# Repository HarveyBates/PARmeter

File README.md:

# PARmeter
## Introduction

**P**hotosynthetic **A**ctive **R**adiation (**PAR**) meters are designed to measure light intensity that has a wavelength between ~400 and 700 nm. This range represents the usable range for photosynthesising organims. This information is important for (amongst other things):

1. Studying photosynthesis
2. Calibrating plant growth light fixtures
3. Calibrating aqurarium LED arrays 

Readings are usually represented as the number of moles of photons per meter squared per second (**&mu;E m<sup>-2</sup> s<sup>-1</sup>** or **&mu;mol m<sup>-2</sup> s<sup>-1</sup>**). 

PAR meters differ from **l**uminous fl**ux** (**lux**) meters in that lux meters are typically used to measure wavelengths specific to human vision rather than those avaliable to photosynthesising organisms. Unlike PAR meters, lux meters require different coefficents for different light sources (white light, warm white light, blue, green, cyan etc.); therefore, they need to be calibrated for each light quality used. 

### Photodiode response

PAR meters are quite expensive when compared to lux meters as PAR meters require a virtually flat spectral response between the 400 and 700 nm wavelength range. This spectral response depends upon the photodiode used for detection. Typically, photodiodes have a varied wavelength specific response and as such only a few have ideal characteristics for PAR meters.

For this design I am using the [FDS100](https://www.thorlabs.com/thorproduct.cfm?partnumber=FDS100) (Silicon Photodiode) from ThorLabs. As its response is farily linear through the wavelength ranges of PAR. The increase in responsitivity with increasing wavelength is as a result of increasing [photon energy](https://en.wikipedia.org/wiki/Photon_energy).

### Cutoff filter

As can be seen from the photodiode responsitivity figure, the FDS100 photodiode is very responsive in wavelengths greater than 700 nm, therefore it is important that a short-pass filter is used to block these wavelengths from reaching the detector. 

Here I am using a 750 nm [short-pass filter](https://www.edmundoptics.com/p/750nm-125mm-dia-od-20-shortpass-filter/43482/) from Edmund optics. 750 nm is greater than the 400 - 700 nm range I mentioned earlier. However, the PAR range that is commonly used was determined a long time ago and there is evidence in the literature that IR-wavlengths are important to photosynthesis.

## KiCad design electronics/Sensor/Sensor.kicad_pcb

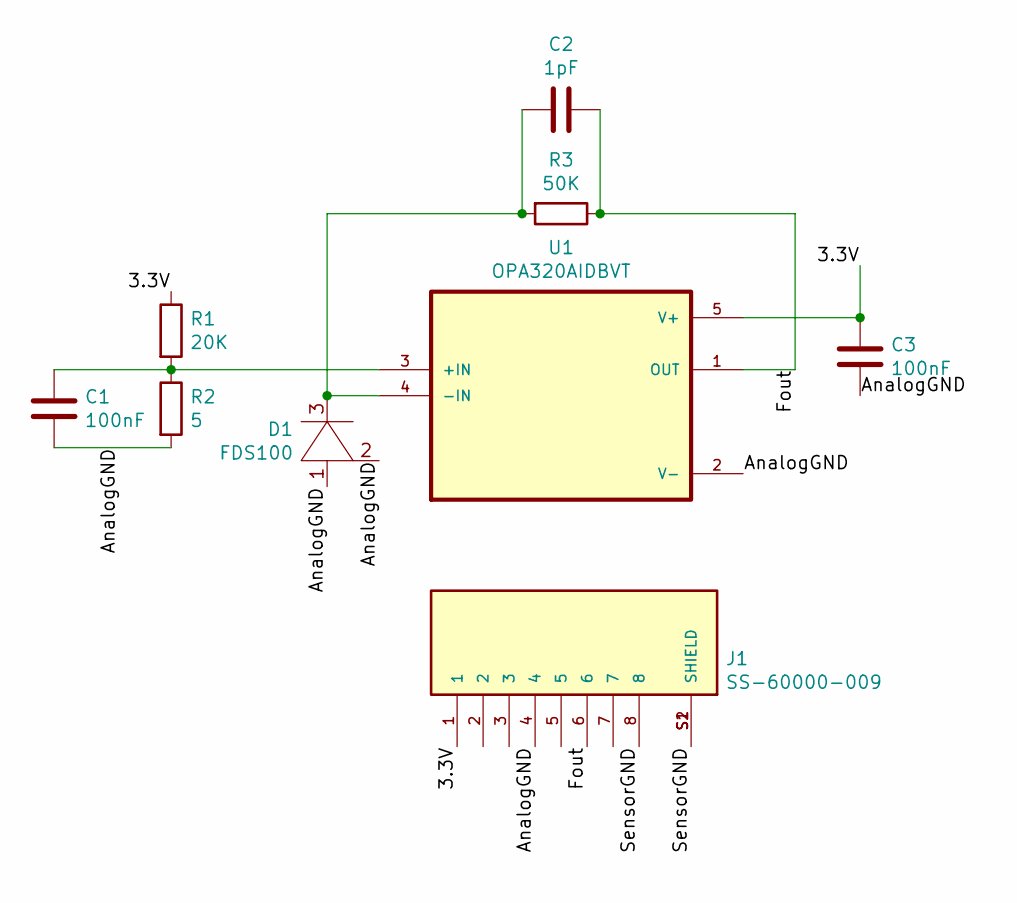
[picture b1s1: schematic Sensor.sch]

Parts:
C1, C3: 100nF; C_0805_2012Metric_Pad1.18x1.45mm_HandSolder
C2: 1pF; C_0805_2012Metric_Pad1.18x1.45mm_HandSolder
D1: FDS100
J1: SS-60000-009; BEL_SS-60000-009; PARTREV D4
R1: 20K; R_0805_2012Metric_Pad1.20x1.40mm_HandSolder
R2: 5; R_0805_2012Metric_Pad1.20x1.40mm_HandSolder
R3: 50K; R_0805_2012Metric_Pad1.20x1.40mm_HandSolder
U1: OPA320AIDBVT; OPA320AIDBVT5-SOT-23

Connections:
/3.3V: C3.2, J1.1, R1.1, U1.5 (V+)
/AnalogGND: C1.2, C3.1, D1.1, D1.2, J1.4, R2.2, U1.2 (V-)
/Fout: C2.1, J1.6, R3.1, U1.1 (OUT)
/SensorGND: J1.8, J1.S1 (SHIELD), J1.S2 (SHIELD)
unnamed: C1.1, R1.2, R2.1, U1.3 (+IN)
unnamed: C2.2, D1.3, R3.2, U1.4 (-IN)

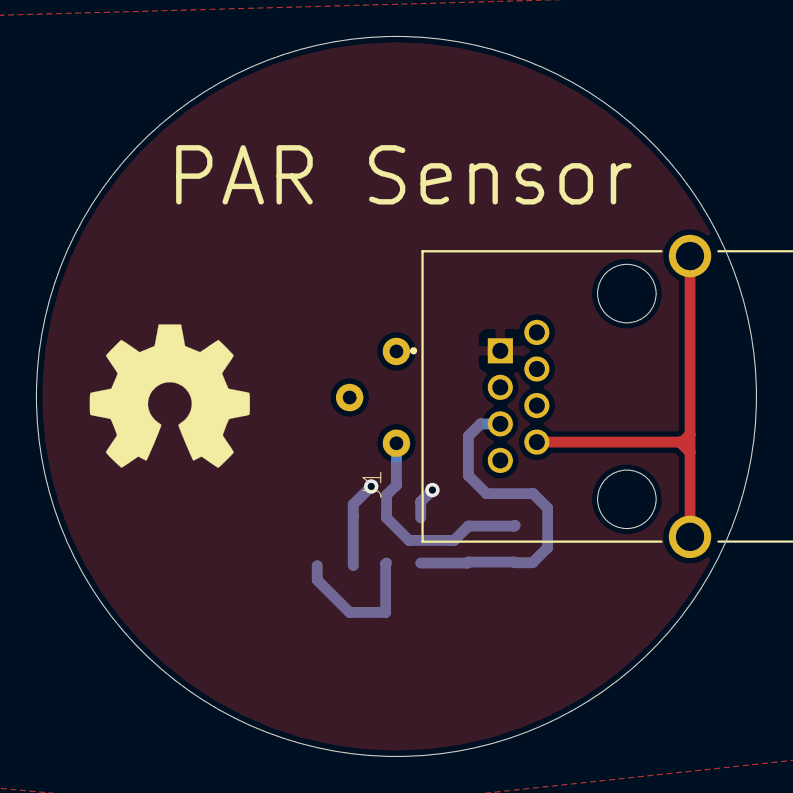
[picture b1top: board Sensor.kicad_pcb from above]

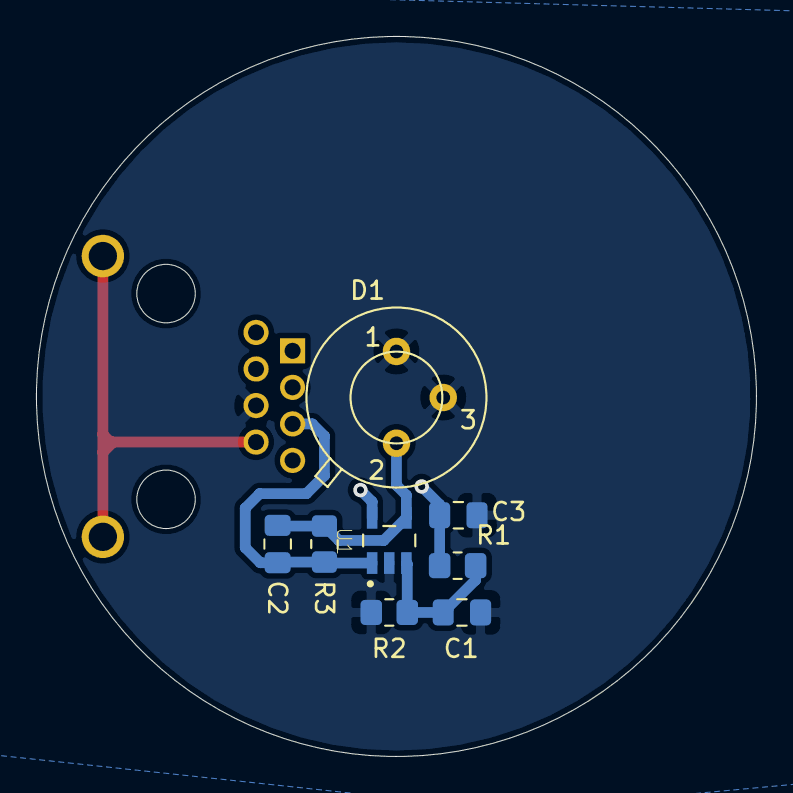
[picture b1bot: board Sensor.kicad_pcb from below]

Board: 2 copper layers, 40.0 x 40.0 mm, 9 parts (8 on the bottom side), 6 nets.

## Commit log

2021-03-10 Create LICENSE
2021-03-10 Update LICENSE
2021-03-10 add notes
2021-03-10 added notes
2021-03-10 create circuit board
2021-03-10 removed cache
2021-03-10 rm kicad folders
2021-03-10 split controller and sensor + add gerbers
2021-03-11 added models and update readme
